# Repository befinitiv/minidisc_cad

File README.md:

# Minidisc

This repository contains the CAD files (PCB & mechanics) for the 8cm "minidisc" player project.

The PCB is designed using Kicad 8, the mechanics is designed using build123d.

## Buld123d environment installation

1. Install direnv
2. Go into the mech/ subfolder, so that the Python environment specified in .envrc file is loaded
3. Install packages: `pip install -r requirements.txt`
4. Start GUI: `jupyter lab`

# BOM
* Display: https://www.reichelt.de/grafik-oled-0-84-zoll-96x16-dot-weiss-ziff-ea-w096016-xblw-p364744.html?&nbc=1
* Bluray drive: https://www.reichelt.de/verbatim-externer-slimline-blu-ray-brenner-verbatim-43889-p264365.html?search=bluray
* Battery: https://www.reichelt.de/mp3-player-akku-fuer-apple-ipod-li-po-1043-mah-akku-30933-p224503.html?&trstct=pos_0&nbc=1
* All other parts are within the Kicad PCB BOM

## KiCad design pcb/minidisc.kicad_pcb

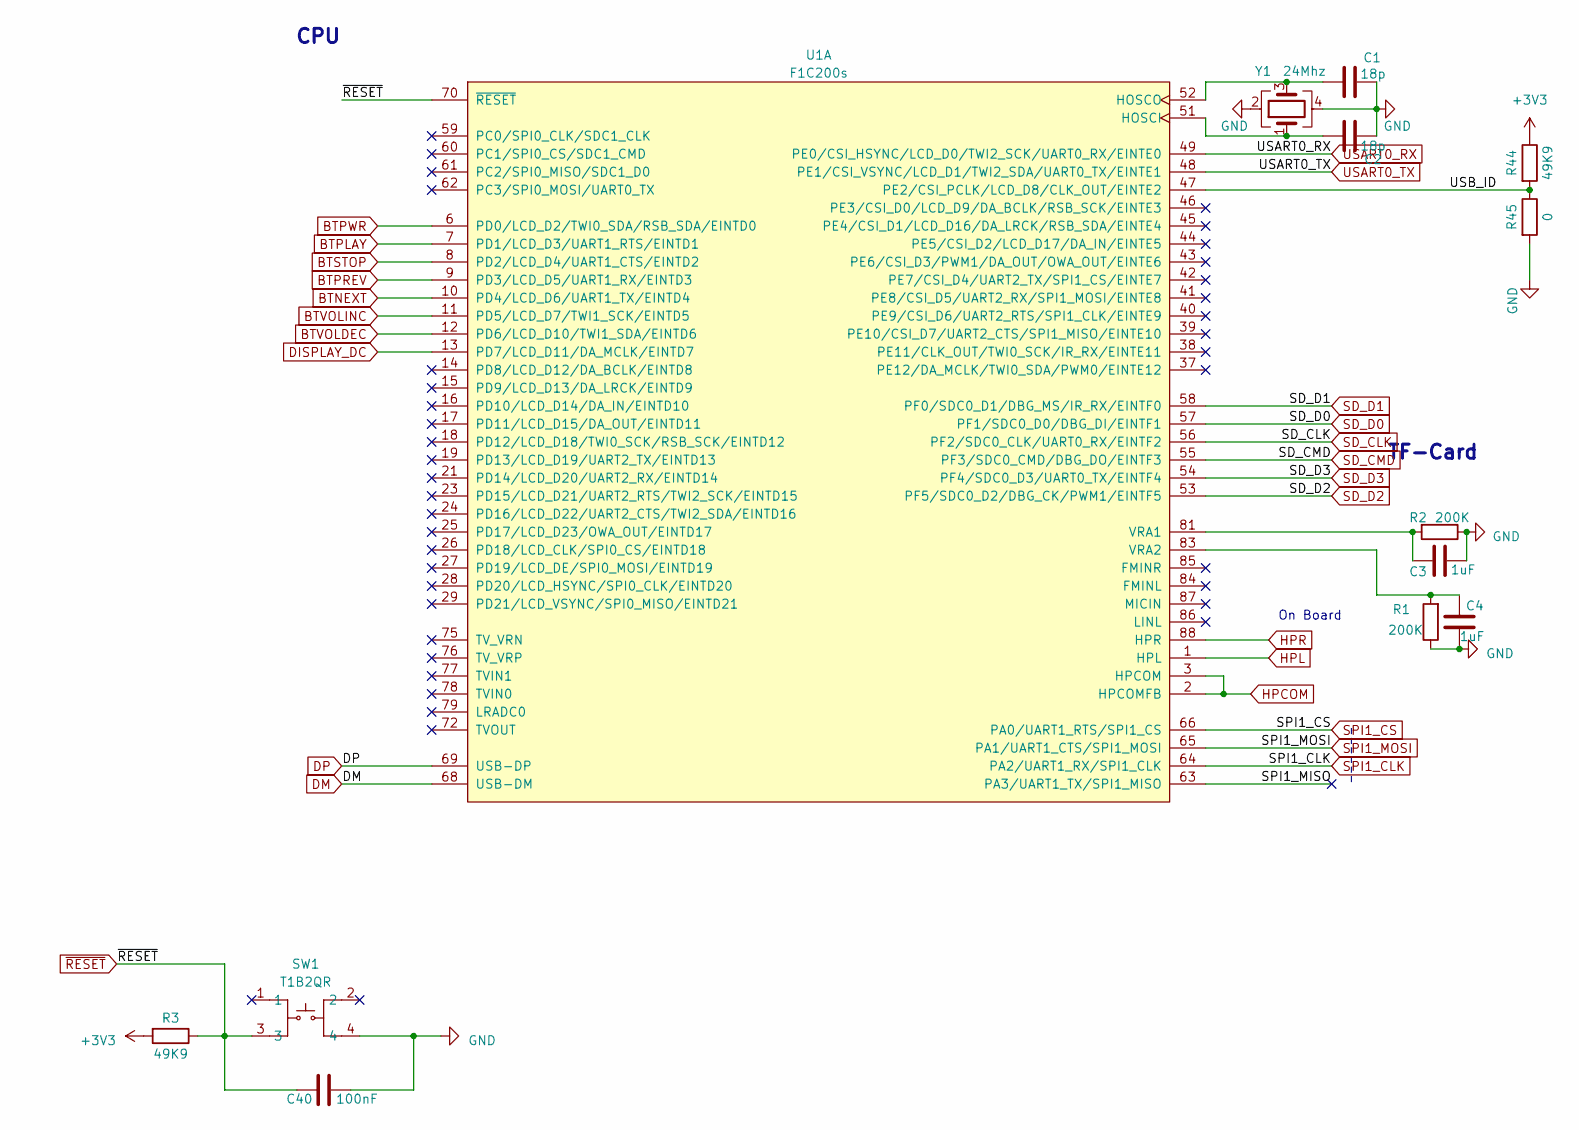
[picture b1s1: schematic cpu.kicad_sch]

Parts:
C1, C2: 18p; C_0402_1005Metric
C3, C4: 1uF; C_0402_1005Metric
C40: 100nF; C_0402_1005Metric_Pad0.74x0.62mm_HandSolder
R1, R2: 200K; R_0402_1005Metric_Pad0.72x0.64mm_HandSolder
R3, R44: 49K9; R_0402_1005Metric_Pad0.72x0.64mm_HandSolder
R45: 0; R_0402_1005Metric_Pad0.72x0.64mm_HandSolder
SW1: T1B2QR; KEY-SMD_4P-L2.6-W1.6-P0.80-LS3.0-1; LCSC Part C495946
U1: F1C200s; QFN-88_L10.0-W10.0-P0.40-BL-EP6.75
Y1: 24Mhz; Crystal_SMD_3225-4Pin_3.2x2.5mm; LCSC C5160135

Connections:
+3V3: R3.2, R44.1; also elsewhere on the board
/cpu/SPI1_MISO: U1.63 (PA3/UART1_TX/SPI1_MISO)
/cpu/USB_ID: R44.2, R45.1, U1.47 (PE2/CSI_PCLK/LCD_D8/CLK_OUT/EINTE2)
BTNEXT: U1.10 (PD4/LCD_D6/UART1_TX/EINTD4); also elsewhere on the board
BTPLAY: U1.7 (PD1/LCD_D3/UART1_RTS/EINTD1); also elsewhere on the board
BTPREV: U1.9 (PD3/LCD_D5/UART1_RX/EINTD3); also elsewhere on the board
BTPWR: U1.6 (PD0/LCD_D2/TWI0_SDA/RSB_SDA/EINTD0); also elsewhere on the board
BTSTOP: U1.8 (PD2/LCD_D4/UART1_CTS/EINTD2); also elsewhere on the board
BTVOLDEC: U1.12 (PD6/LCD_D10/TWI1_SDA/EINTD6); also elsewhere on the board
BTVOLINC: U1.11 (PD5/LCD_D7/TWI1_SCK/EINTD5); also elsewhere on the board
DISPLAY_DC: U1.13 (PD7/LCD_D11/DA_MCLK/EINTD7); also elsewhere on the board
DM: U1.68 (USB-DM); also elsewhere on the board
DP: U1.69 (USB-DP); also elsewhere on the board
GND: C1.1, C2.1, C3.1, C4.1, C40.2, R1.1, R2.1, R45.2, SW1.4, Y1.2, Y1.4; also elsewhere on the board
HPCOM: U1.2 (HPCOMFB), U1.3 (HPCOM); also elsewhere on the board
HPL: U1.1 (HPL); also elsewhere on the board
HPR: U1.88 (HPR); also elsewhere on the board
unnamed: C2.2, U1.51 (HOSCI), Y1.1
unnamed: C1.2, U1.52 (HOSCO), Y1.3
unnamed: C3.2, R2.2, U1.81 (VRA1)
unnamed: C4.2, R1.2, U1.83 (VRA2)
SD_D0: U1.57 (PF1/SDC0_D0/DBG_DI/EINTF1); also elsewhere on the board
SD_D1: U1.58 (PF0/SDC0_D1/DBG_MS/IR_RX/EINTF0); also elsewhere on the board
SD_D2: U1.53 (PF5/SDC0_D2/DBG_CK/PWM1/EINTF5); also elsewhere on the board
SD_D3: U1.54 (PF4/SDC0_D3/UART0_TX/EINTF4); also elsewhere on the board
SPI1_CLK: U1.64 (PA2/UART1_RX/SPI1_CLK); also elsewhere on the board
SPI1_CS: U1.66 (PA0/UART1_RTS/SPI1_CS); also elsewhere on the board
SPI1_MOSI: U1.65 (PA1/UART1_CTS/SPI1_MOSI); also elsewhere on the board
USART0_RX: U1.49 (PE0/CSI_HSYNC/LCD_D0/TWI2_SCK/UART0_RX/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); also elsewhere on the board
USART0_TX: U1.48 (PE1/CSI_VSYNC/LCD_D1/TWI2_SDA/UART0_TX/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); also elsewhere on the board
~RESET: C40.1, R3.1, SW1.3, U1.70 (~RESET); also elsewhere on the board

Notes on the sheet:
On Board
TF-Card
CPU

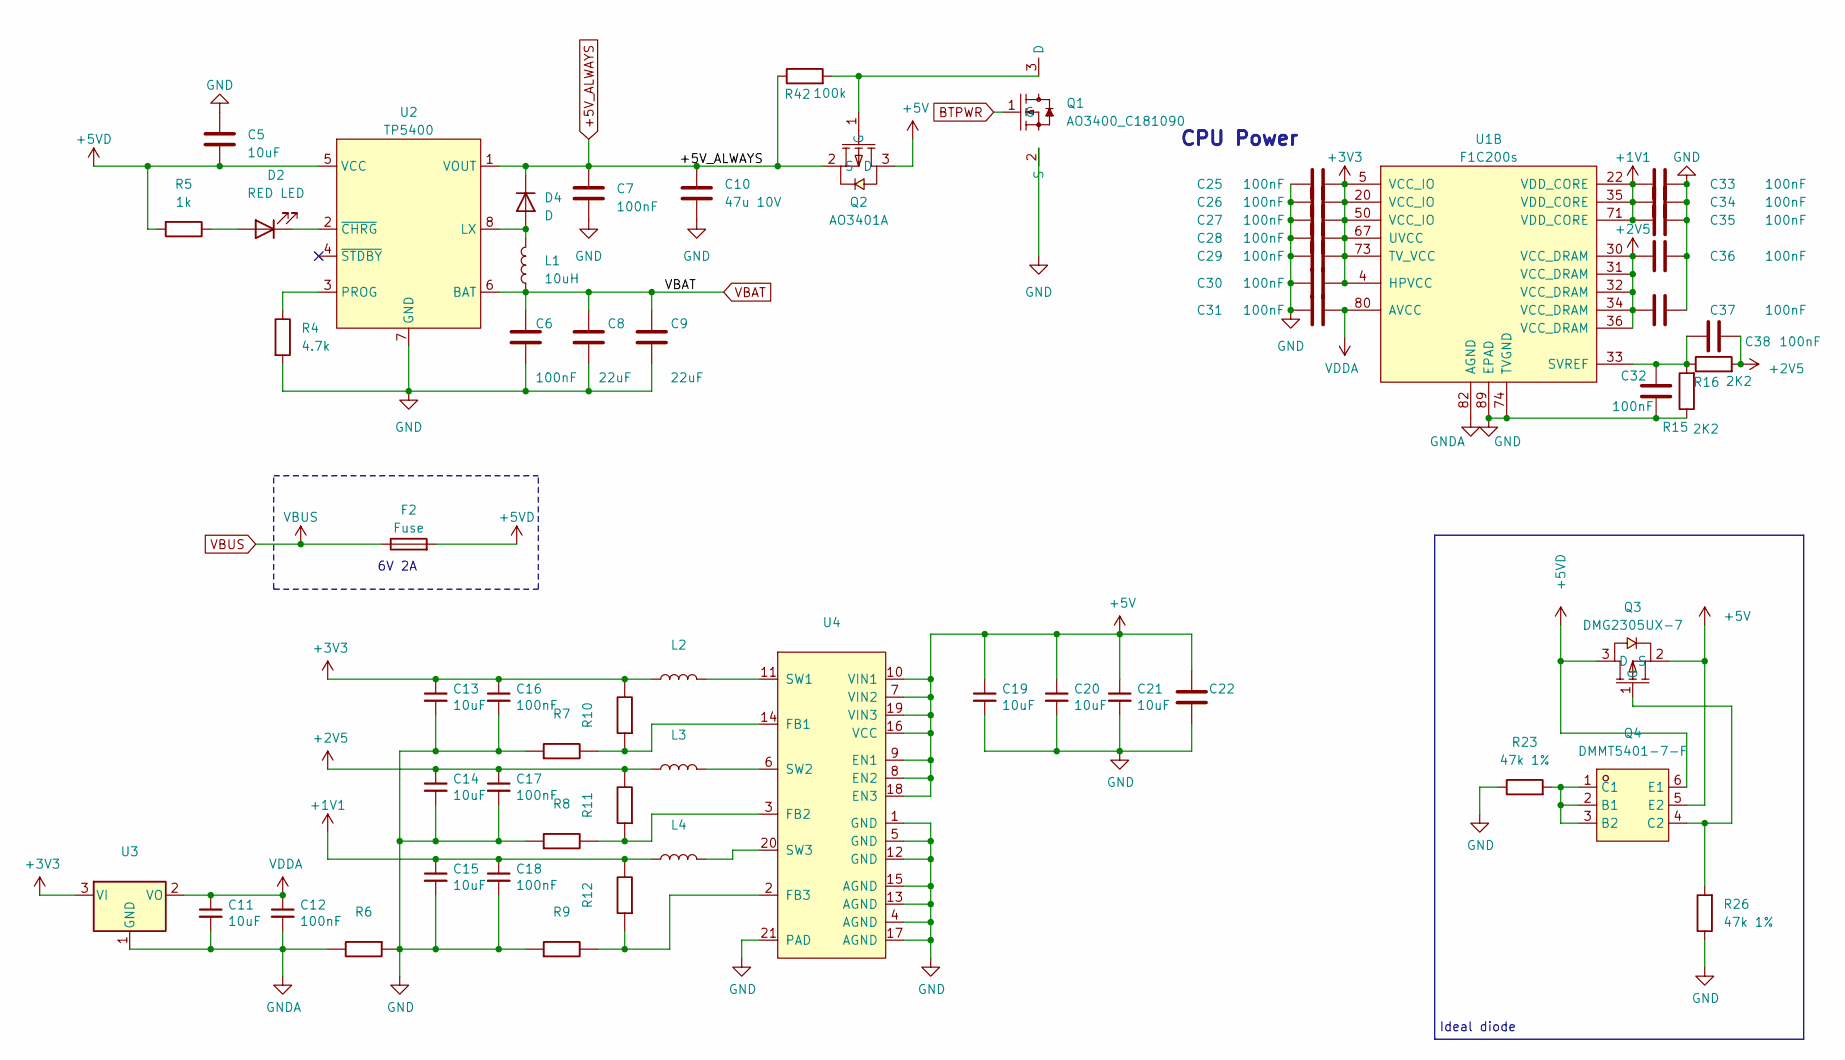
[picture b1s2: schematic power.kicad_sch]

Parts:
C5: 10uF; C_0603_1608Metric
C6: 100nF; C_0402_1005Metric
C7, C25, C26, C27, C28, C29, C30, C31, C32, C33, C34, C35, C36, C37, C38: 100nF; C_0402_1005Metric_Pad0.74x0.62mm_HandSolder
C8, C9: 22uF; C_0805_2012Metric
C10, C22: 47u 10V; C_1210_3225Metric
C11, C13, C14, C15, C19, C20, C21: 03.4004_C0603_10uF; C_0603_1608Metric
C12, C16, C17: 03.0009_C0402_100nF; C_0402_1005Metric
C18: 03.0009_C0402_100nF; R_0402_1005Metric
D2: RED LED; LED_0402_1005Metric
D4: D; D_SMA; LCSC C34897
F2: Fuse; Fuse_1206_3216Metric; LCSC C720076
L1: 10uH; IND-SMD_L4.0-W4.0
L2, L3, L4: 06.0102_L2520_2.2uH; L_1008_2520Metric; LCSC C315721
Q1: AO3400_C181090; SOT-23-3_L2.9-W1.3-P1.90-LS2.4-BR; LCSC Part C181090
Q2: AO3401A; SOT-23_L2.9-W1.3-P1.90-LS2.4-BR; LCSC Part C15127
Q3: DMG2305UX-7; SOT-23-3_L2.9-W1.3-P1.90-LS2.4-BR; LCSC Part C150470
Q4: DMMT5401-7-F; SOT-23-6_L2.9-W1.6-P0.95-LS2.8-BR; LCSC Part C154733
R4: 4.7k; R_0402_1005Metric
R5: 1k; R_0402_1005Metric
R6: 0; R_0402_1005Metric
R7, R8, R9, R12: 150K 1%; R_0402_1005Metric; LCSC C3015896
R10: 680K 1%; R_0402_1005Metric; LCSC C2909377
R11: 470K 1%; R_0402_1005Metric
R15, R16: 2K2; R_0402_1005Metric_Pad0.72x0.64mm_HandSolder
R23, R26: 47k 1%; R_0402_1005Metric
R42: 100k; R_0402_1005Metric_Pad0.72x0.64mm_HandSolder
U1: F1C200s; QFN-88_L10.0-W10.0-P0.40-BL-EP6.75
U2: TP5400; ESOP-8_L4.9-W3.9-P1.27-LS6.0-BL-EP
U3: 09.0103_XC6206; SOT-23; LCSC C347375
U4: 09.0102_EA3036; WQFN-20-1EP_3x3mm_P0.4mm_EP1.7x1.7mm_ThermalVias; LCSC C570857

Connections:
+1V1: C15.1, C18.1, C33.1, C34.1, C35.1, L4.1, R12.2, U1.22 (VDD_CORE), U1.35 (VDD_CORE), U1.71 (VDD_CORE)
+2V5: C14.1, C17.1, C36.1, C37.1, C38.1, L3.1, R11.2, R16.2, U1.30 (VCC_DRAM), U1.31 (VCC_DRAM), U1.32 (VCC_DRAM), U1.34 (VCC_DRAM), U1.36 (VCC_DRAM)
+3V3: C13.1, C16.1, C25.2, C26.2, C27.2, C28.2, C29.2, C30.2, L2.1, R10.2, U1.4 (HPVCC), U1.5 (VCC_IO), U1.20 (VCC_IO), U1.50 (VCC_IO), U1.67 (UVCC), U1.73 (TV_VCC), U3.3 (VI); also elsewhere on the board
+5V: C19.1, C20.1, C21.1, C22.1, Q2.3 (D), Q3.2 (S), Q4.5 (E2), U4.7 (VIN2), U4.8 (EN2), U4.9 (EN1), U4.10 (VIN1), U4.16 (VCC), U4.18 (EN3), U4.19 (VIN3); also elsewhere on the board
+5VD: C5.2, F2.2, Q3.3 (D), Q4.6 (E1), R5.2, U2.5 (VCC); also elsewhere on the board
+5V_ALWAYS: C7.1, C10.1, D4.1 (K), Q2.2 (S), R42.1, U2.1 (VOUT); also elsewhere on the board
BTPWR: Q1.1 (G); also elsewhere on the board
GND: C5.1, C6.2, C7.2, C8.2, C9.2, C10.2, C13.2, C14.2, C15.2, C16.2, C17.2, C18.2, C19.2, C20.2, C21.2, C22.2, C25.1, C26.1, C27.1, C28.1, C29.1, C30.1, C31.1, C32.1, C33.2, C34.2, C35.2, C36.2, C37.2, Q1.2 (S), R4.2, R6.1, R7.1, R8.1, R9.1, R15.1, R23.1, R26.1, U1.74 (TVGND), U1.89 (EPAD), U2.7 (GND), U4.1 (GND), U4.4 (AGND), U4.5 (GND), U4.12 (GND), U4.13 (AGND), U4.15 (AGND), U4.17 (AGND), U4.21 (PAD); also elsewhere on the board
GNDA: C11.2, C12.2, R6.2, U1.82 (AGND), U3.1 (GND)
unnamed: D2.2 (A), R5.1
unnamed: D2.1 (K), U2.2 (~CHRG)
unnamed: D4.2 (A), L1.1, U2.8 (LX)
unnamed: Q1.3 (D), Q2.1 (G), R42.2
unnamed: Q3.1 (G), Q4.4 (C2), R26.2
unnamed: Q4.1 (C1), Q4.2 (B1), Q4.3 (B2), R23.2
unnamed: C32.2, C38.2, R15.2, R16.1, U1.33 (SVREF)
unnamed: R4.1, U2.3 (PROG)
unnamed: R7.2, R10.1, U4.14 (FB1)
unnamed: R8.2, R11.1, U4.3 (FB2)
unnamed: R9.2, R12.1, U4.2 (FB3)
unnamed: L2.2, U4.11 (SW1)
unnamed: L3.2, U4.6 (SW2)
unnamed: L4.2, U4.20 (SW3)
VBAT: C6.1, C8.1, C9.1, L1.2, U2.6 (BAT); also elsewhere on the board
VBUS: F2.1; also elsewhere on the board
VDDA: C11.1, C12.1, C31.2, U1.80 (AVCC), U3.2 (VO)

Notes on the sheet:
6V 2A
CPU Power
Ideal diode

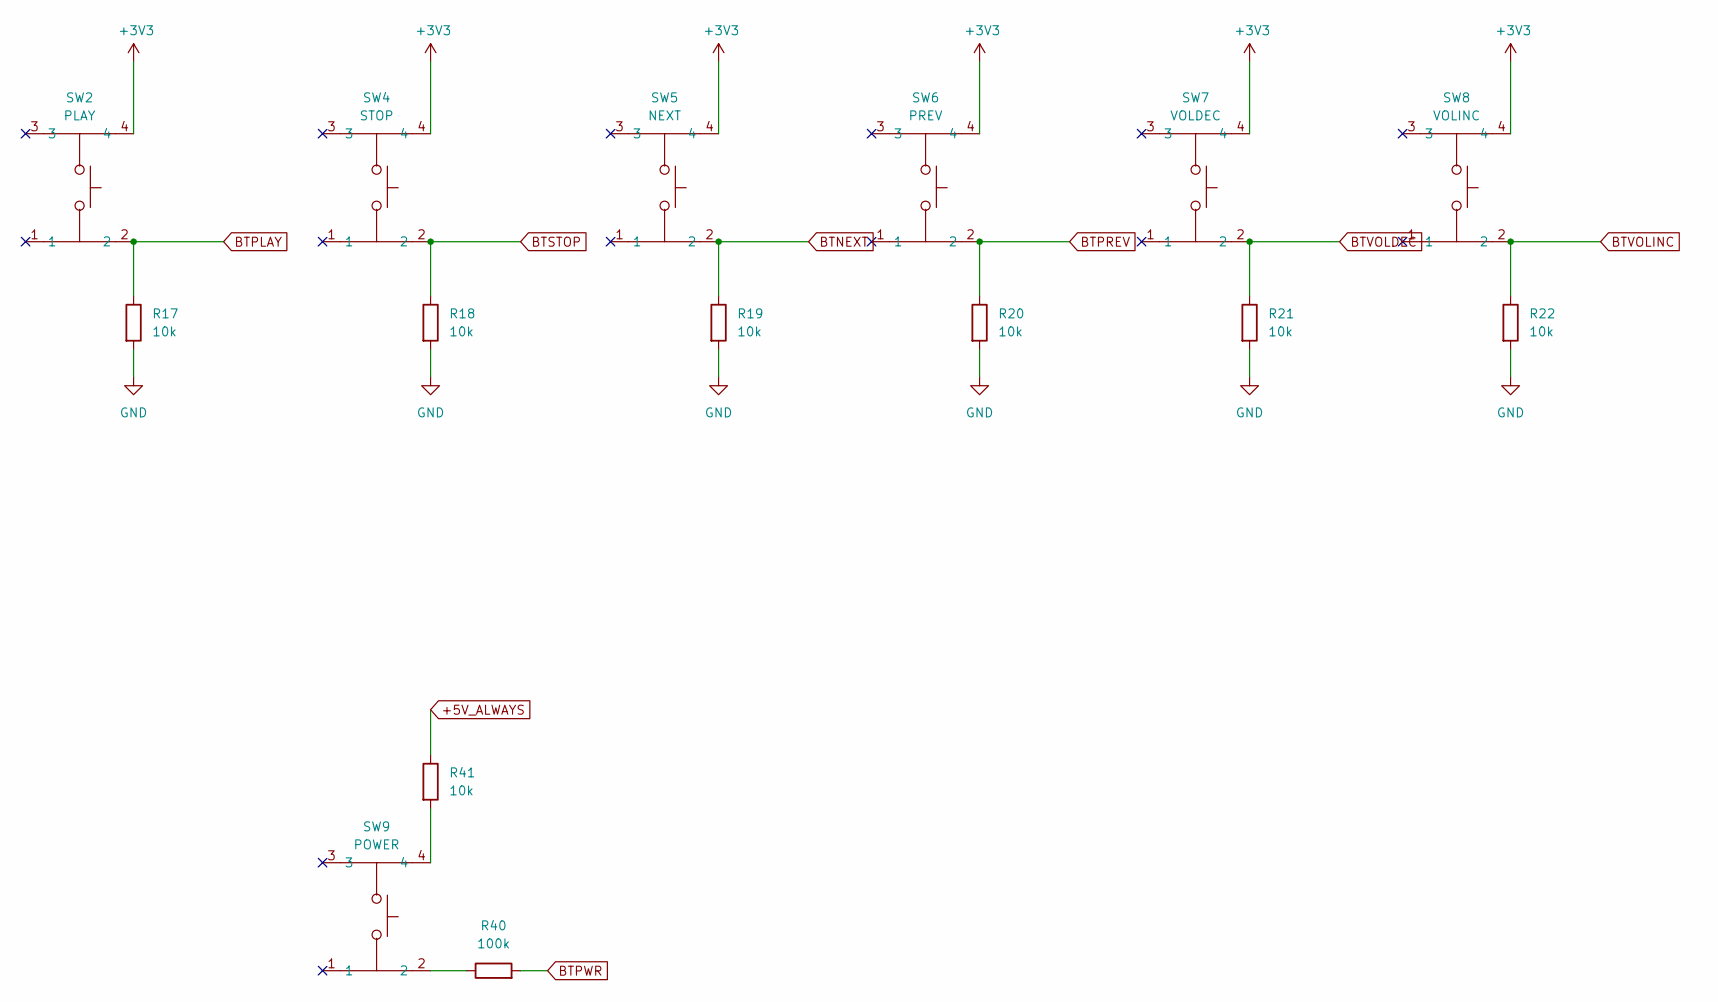
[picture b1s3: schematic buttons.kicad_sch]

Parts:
R17, R18, R19, R20, R21, R22, R41: 10k; R_0402_1005Metric
R40: 100k; R_0402_1005Metric
SW2: PLAY; SW-SMD_4P-L3.5-W2.9-P1.30-LS4.8; LCSC Part C130445
SW4: STOP; SW-SMD_4P-L3.5-W2.9-P1.30-LS4.8; LCSC Part C130445
SW5: NEXT; SW-SMD_4P-L3.5-W2.9-P1.30-LS4.8; LCSC Part C130445
SW6: PREV; SW-SMD_4P-L3.5-W2.9-P1.30-LS4.8; LCSC Part C130445
SW7: VOLDEC; SW-SMD_4P-L3.5-W2.9-P1.30-LS4.8; LCSC Part C130445
SW8: VOLINC; SW-SMD_4P-L3.5-W2.9-P1.30-LS4.8; LCSC Part C130445
SW9: POWER; SW-SMD_4P-L3.5-W2.9-P1.30-LS4.8; LCSC Part C130445

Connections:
+3V3: SW2.4, SW4.4, SW5.4, SW6.4, SW7.4, SW8.4; also elsewhere on the board
+5V_ALWAYS: R41.1; also elsewhere on the board
BTNEXT: R19.1, SW5.2; also elsewhere on the board
BTPLAY: R17.1, SW2.2; also elsewhere on the board
BTPREV: R20.1, SW6.2; also elsewhere on the board
BTPWR: R40.2; also elsewhere on the board
BTSTOP: R18.1, SW4.2; also elsewhere on the board
BTVOLDEC: R21.1, SW7.2; also elsewhere on the board
BTVOLINC: R22.1, SW8.2; also elsewhere on the board
GND: R17.2, R18.2, R19.2, R20.2, R21.2, R22.2; also elsewhere on the board
unnamed: R40.1, SW9.2
unnamed: R41.2, SW9.4

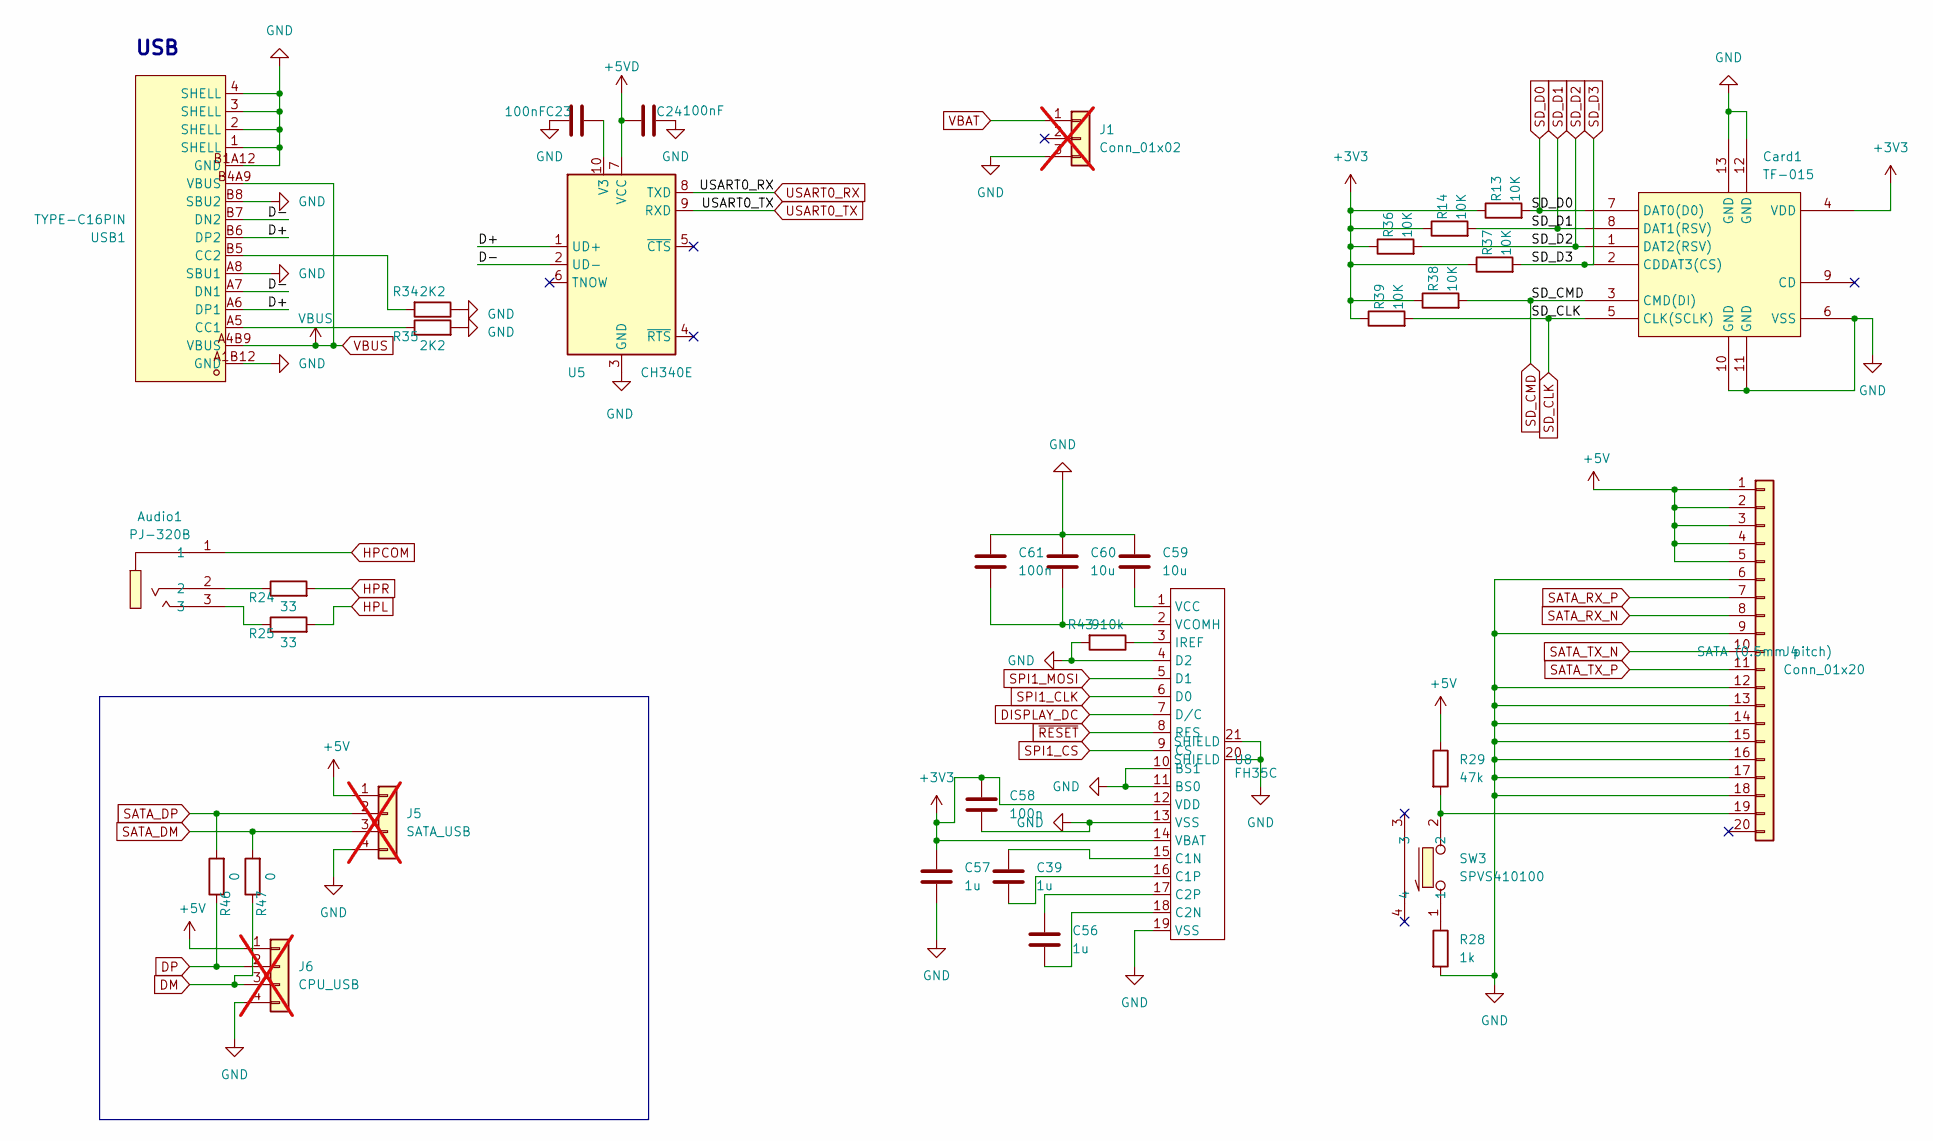
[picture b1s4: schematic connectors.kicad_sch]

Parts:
Audio1: PJ-320B; AUDIO-SMD_PJ-320B; LCSC Part C18594
C23, C24: 100nF; C_0402_1005Metric_Pad0.74x0.62mm_HandSolder
C39, C56, C57: 1u; C_0402_1005Metric
C58, C61: 100n; C_0402_1005Metric
C59, C60: 10u; C_0603_1608Metric
Card1: TF-015; TF-SMD_TF-015; LCSC Part C113206
J1: Conn_01x02; ipodbattery; not fitted
J4: Conn_01x20; Hirose_FH12-20S-0.5SH_1x20-1MP_P0.50mm_Horizontal; LCSC C596730
J5: SATA_USB; PinHeader_1x04_P1.00mm_Vertical; not fitted
J6: CPU_USB; PinHeader_1x04_P1.00mm_Vertical; not fitted
R13, R14, R36, R37, R38, R39: 10K; R_0402_1005Metric_Pad0.72x0.64mm_HandSolder
R24, R25: 33; R_0402_1005Metric_Pad0.72x0.64mm_HandSolder
R28: 1k; R_0402_1005Metric
R29: 47k; R_0402_1005Metric
R34, R35: 2K2; R_0402_1005Metric_Pad0.72x0.64mm_HandSolder
R43: 910k; R_0402_1005Metric_Pad0.72x0.64mm_HandSolder
R46, R47: 0; R_0402_1005Metric_Pad0.72x0.64mm_HandSolder
SW3: SPVS410100; SW-SMD_SPVS410100; LCSC Part C160857
U5: CH340E; MSOP-10_3x3mm_P0.5mm
U8: FH35C; FPC-SMD_19P-P0.60_HRS_FH35C-19S-0.3SHW
USB1: TYPE-C16PIN; USB-C-SMD_TYPE-C16PIN; LCSC Part C393939

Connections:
+3V3: C57.1, C58.1, Card1.4 (VDD), R13.1, R14.1, R36.1, R37.1, R38.1, R39.1, U8.12 (VDD), U8.14 (VBAT); also elsewhere on the board
+5V: J4.1, J4.2, J4.3, J4.4, J4.5, J5.1, J6.1, R29.1; also elsewhere on the board
+5VD: C24.1, U5.7 (VCC); also elsewhere on the board
/connectors/D+: U5.1 (UD+), USB1.A6 (DP1), USB1.B6 (DP2)
/connectors/D-: U5.2 (UD-), USB1.A7 (DN1), USB1.B7 (DN2)
DISPLAY_DC: U8.7 (D/C); also elsewhere on the board
DM: J6.3, R47.1; also elsewhere on the board
DP: J6.2, R46.1; also elsewhere on the board
GND: C23.2, C24.2, C57.2, C58.2, C59.1, C60.1, C61.1, Card1.6 (VSS), Card1.10 (GND), Card1.11 (GND), Card1.12 (GND), Card1.13 (GND), J1.3, J4.6, J4.9, J4.12, J4.13, J4.14, J4.15, J4.16, J4.17, J4.18, J5.4, J6.4, R28.2, R34.1, R35.2, R43.2, U5.3 (GND), U8.4 (D2), U8.10 (BS1), U8.11 (BS0), U8.13 (VSS), U8.19 (VSS), U8.20 (SHIELD), U8.21 (SHIELD), USB1.1 (SHELL), USB1.2 (SHELL), USB1.3 (SHELL), USB1.4 (SHELL), USB1.A1B12 (GND), USB1.A8 (SBU1), USB1.B1A12 (GND), USB1.B8 (SBU2); also elsewhere on the board
HPCOM: Audio1.1; also elsewhere on the board
HPL: R25.2; also elsewhere on the board
HPR: R24.2; also elsewhere on the board
unnamed: Audio1.2, R24.1
unnamed: Audio1.3, R25.1
unnamed: J4.19, R29.2, SW3.2
unnamed: R28.1, SW3.1
unnamed: C23.1, U5.10 (V3)
unnamed: C39.1, U8.15 (C1N)
unnamed: C39.2, U8.16 (C1P)
unnamed: C56.2, U8.18 (C2N)
unnamed: C56.1, U8.17 (C2P)
unnamed: R43.1, U8.3 (IREF)
unnamed: C59.2, U8.1 (VCC)
unnamed: C60.2, C61.2, U8.2 (VCOMH)
unnamed: R35.1, USB1.A5 (CC1)
unnamed: R34.2, USB1.B5 (CC2)
SATA_DM: J5.3, R47.2; also elsewhere on the board
SATA_DP: J5.2, R46.2; also elsewhere on the board
SATA_RX_N: J4.8; also elsewhere on the board
SATA_RX_P: J4.7; also elsewhere on the board
SATA_TX_N: J4.10; also elsewhere on the board
SATA_TX_P: J4.11; also elsewhere on the board
SD_D0: Card1.7 (DAT0(D0)), R13.2; also elsewhere on the board
SD_D1: Card1.8 (DAT1(RSV)), R14.2; also elsewhere on the board
SD_D2: Card1.1 (DAT2(RSV)), R36.2; also elsewhere on the board
SD_D3: Card1.2 (CDDAT3(CS)), R37.2; also elsewhere on the board
SPI1_CLK: U8.6 (D0); also elsewhere on the board
SPI1_CS: U8.9 (CS); also elsewhere on the board
SPI1_MOSI: U8.5 (D1); also elsewhere on the board
USART0_RX: U5.8 (TXD); also elsewhere on the board
USART0_TX: U5.9 (RXD); also elsewhere on the board
VBAT: J1.1; also elsewhere on the board
VBUS: USB1.A4B9 (VBUS), USB1.B4A9 (VBUS); also elsewhere on the board
~RESET: U8.8 (RES); also elsewhere on the board

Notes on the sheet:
USB

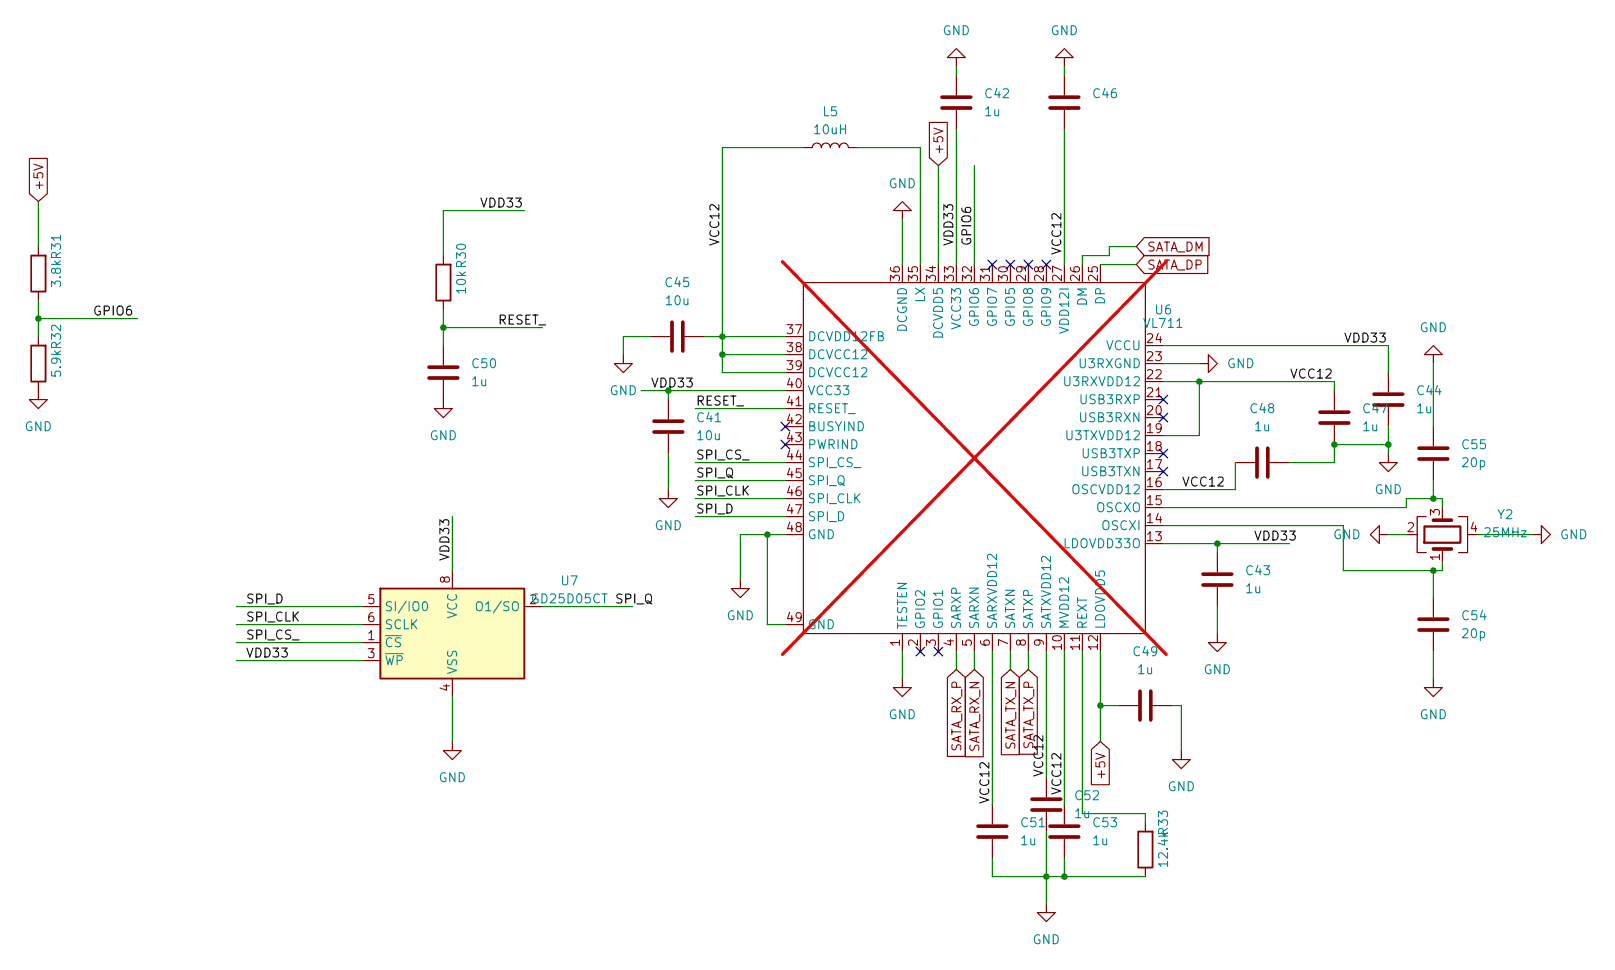
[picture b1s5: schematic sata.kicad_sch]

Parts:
C41, C45: 10u; C_0603_1608Metric
C42, C43, C44, C46, C47, C48, C49, C50, C51, C52, C53: 1u; C_0402_1005Metric
C54, C55: 20p; C_0402_1005Metric
L5: 10uH; L_1206_3216Metric
R30: 10k; R_0402_1005Metric_Pad0.72x0.64mm_HandSolder
R31: 3.8k; R_0402_1005Metric_Pad0.72x0.64mm_HandSolder; LCSC C102983
R32: 5.9k; R_0402_1005Metric_Pad0.72x0.64mm_HandSolder
R33: 12.4k; R_0402_1005Metric_Pad0.72x0.64mm_HandSolder
U6: VL711; QFN-48-1EP_6x6mm_P0.4mm_EP4.2x4.2mm_ThermalVias; not fitted
U7: GD25D05CT; SOP-8_3.9x4.9mm_P1.27mm
Y2: 25MHz; Crystal_SMD_3225-4Pin_3.2x2.5mm

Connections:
+5V: C49.1, R31.2, U6.12 (LDOVDD5), U6.34 (DCVDD5); also elsewhere on the board
/sata/GPIO6: R31.1, R32.2, U6.32 (GPIO6)
/sata/RESET_: C50.2, R30.1, U6.41 (RESET_)
/sata/SPI_CLK: U6.46 (SPI_CLK), U7.6 (SCLK)
/sata/SPI_CS_: U6.44 (SPI_CS_), U7.1 (~CS)
/sata/SPI_D: U6.47 (SPI_D), U7.5 (SI/IO0)
/sata/SPI_Q: U6.45 (SPI_Q), U7.2 (O1/SO)
/sata/VCC12: C45.2, C46.2, C47.1, C48.1, C51.2, C52.2, C53.2, L5.1, U6.6 (SARXVDD12), U6.9 (SATXVDD12), U6.10 (MVDD12), U6.16 (OSCVDD12), U6.19 (U3TXVDD12), U6.22 (U3RXVDD12), U6.27 (VDD12I), U6.37 (DCVDD12FB), U6.38 (DCVCC12), U6.39 (DCVCC12)
/sata/VDD33: C41.1, C42.2, C43.1, C44.1, R30.2, U6.13 (LDOVDD33O), U6.24 (VCCU), U6.33 (VCC33), U6.40 (VCC33), U7.3 (~WP), U7.8 (VCC)
GND: C41.2, C42.1, C43.2, C44.2, C45.1, C46.1, C47.2, C48.2, C49.2, C50.1, C51.1, C52.1, C53.1, C54.2, C55.1, R32.1, R33.1, U6.1 (TESTEN), U6.23 (U3RXGND), U6.36 (DCGND), U6.48 (GND), U6.49 (GND), U7.4 (VSS), Y2.2, Y2.4; also elsewhere on the board
unnamed: L5.2, U6.35 (LX)
unnamed: C54.1, U6.14 (OSCXI), Y2.1
unnamed: C55.2, U6.15 (OSCXO), Y2.3
unnamed: R33.2, U6.11 (REXT)
SATA_DM: U6.26 (DM); also elsewhere on the board
SATA_DP: U6.25 (DP); also elsewhere on the board
SATA_RX_N: U6.5 (SARXN); also elsewhere on the board
SATA_RX_P: U6.4 (SARXP); also elsewhere on the board
SATA_TX_N: U6.7 (SATXN); also elsewhere on the board
SATA_TX_P: U6.8 (SATXP); also elsewhere on the board

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
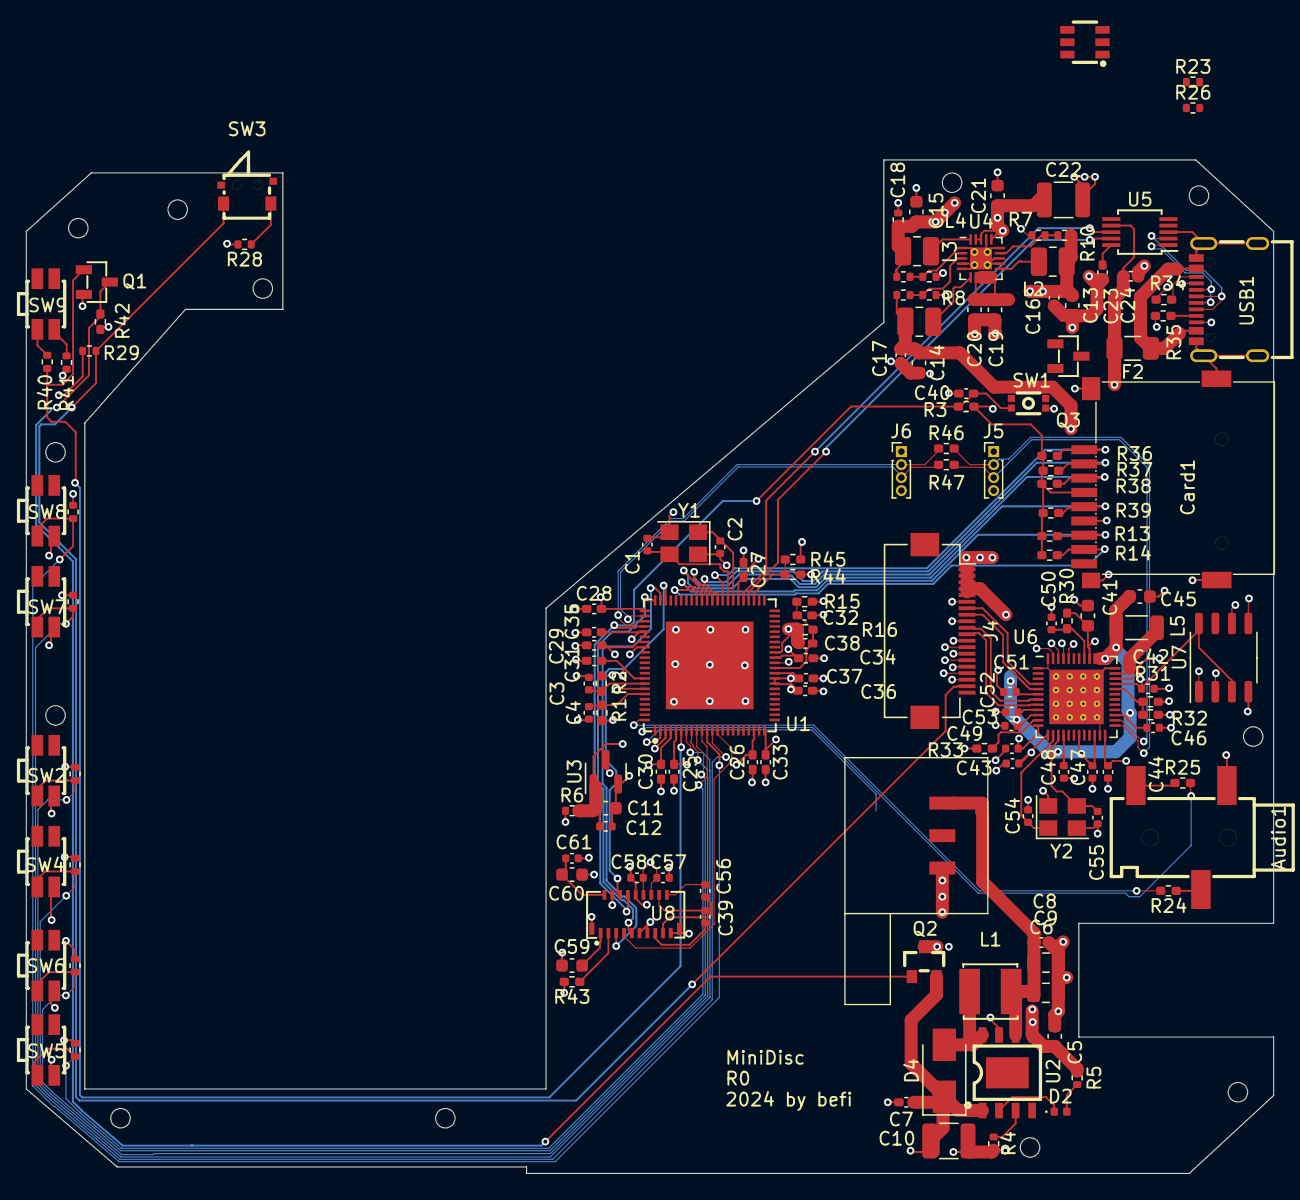
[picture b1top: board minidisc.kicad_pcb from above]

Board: 4 copper layers, 96.0 x 78.0 mm, 145 parts (0 on the bottom side), 91 nets.

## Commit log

2024-04-18 Automated import of PCB screw holes, added holes for switches, usb-C, microsd & audio
2024-04-19 Added README
2024-04-22 Added display cutout and buttons
2024-05-24 Added last minor patches like ideal diode on PCB, added backplate
2024-05-24 Added BOM to readme
